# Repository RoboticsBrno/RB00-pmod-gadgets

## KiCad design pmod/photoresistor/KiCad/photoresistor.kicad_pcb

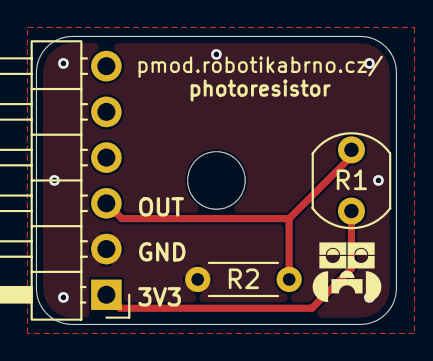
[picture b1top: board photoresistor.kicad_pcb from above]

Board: 2 copper layers, 20.0 x 16.0 mm, 4 parts (0 on the bottom side), 3 nets.

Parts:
H1: MountingHole_Pad; MountingHole_3.2mm_M3_DIN965
J2: Conn_01x06_Pin; PinHeader_1x06_P2.54mm_Horizontal
R1: LDR07; R_LDR_5.1x4.3mm_P3.4mm_Vertical
R2: R; R_Axial_DIN0204_L3.6mm_D1.6mm_P5.08mm_Horizontal

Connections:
+3V3: J2.1, R1.1
GND: J2.2, R2.2
GPIO: J2.3, R1.2, R2.1

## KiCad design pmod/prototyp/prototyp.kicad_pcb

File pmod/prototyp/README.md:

# Prototypovací modul PMOD

Tento modul slouží jako flexibilní platforma pro experimentování a rychlé vytváření prototypů elektronických obvodů. Nabízí základní PMOD konektor pro snadné připojení a testování různých komponent.

[Manuál](manual.md){ .md-button .md-button--primary }

|  |  |
| --- | --- |

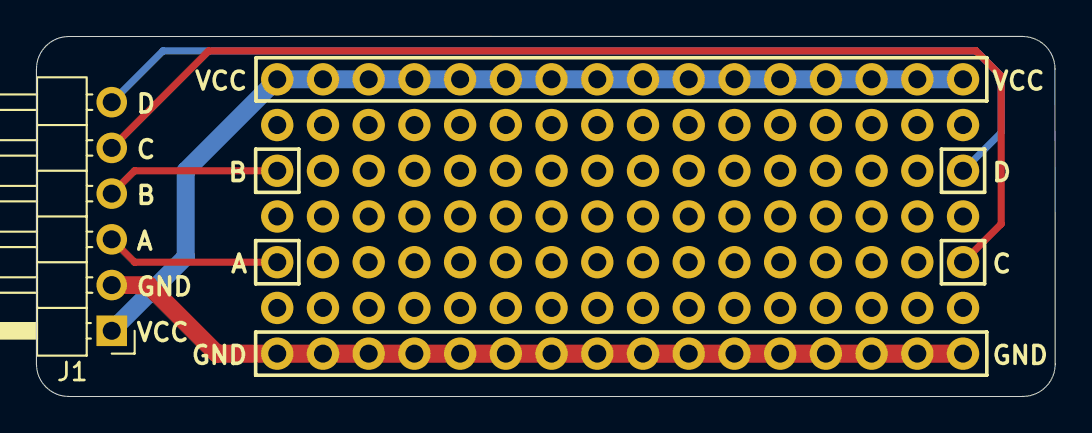
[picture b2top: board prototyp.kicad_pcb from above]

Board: 2 copper layers, 56.6 x 20.0 mm, 113 parts (0 on the bottom side), 6 nets.

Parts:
H1, H2, H3, H4, H5, H6, H7, H8, H9, H10, H11, H12, H13, H14, H15, H16, H17, H18, H19, H20, H21, H22, H23, H24, H25, H26, H27, H28, H29, H30, H31, H32, H33, H34, H35, H36, H37, H38, H39, H40, H41, H42, H43, H44, H45, H46, H47, H48, H49, H50, H51, H52, H53, H54, H55, H56, H57, H58, H59, H60, H61, H62, H63, H64, H65, H66, H67, H68, H69, H70, H71, H72, H73, H74, H75, H76, H77, H78, H79, H80, H81, H82, H83, H84, H85, H86, H87, H88, H89, H90, H91, H92, H93, H94, H95, H96, H97, H98, H99, H100, H101, H102, H103, H104, H105, H106, H107, H108, H109, H110, H111, H112: Hole
J1: Conn_01x06_Pin; PinHeader_1x06_P2.54mm_Horizontal

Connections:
A: H33.1, J1.3
B: H65.1, J1.4
C: H48.1, J1.5
D: H80.1, J1.6
GND: H1.1, H2.1, H3.1, H4.1, H5.1, H6.1, H7.1, H8.1, H9.1, H10.1, H11.1, H12.1, H13.1, H14.1, H15.1, H16.1, J1.2
VCC: H97.1, H98.1, H99.1, H100.1, H101.1, H102.1, H103.1, H104.1, H105.1, H106.1, H107.1, H108.1, H109.1, H110.1, H111.1, H112.1, J1.1

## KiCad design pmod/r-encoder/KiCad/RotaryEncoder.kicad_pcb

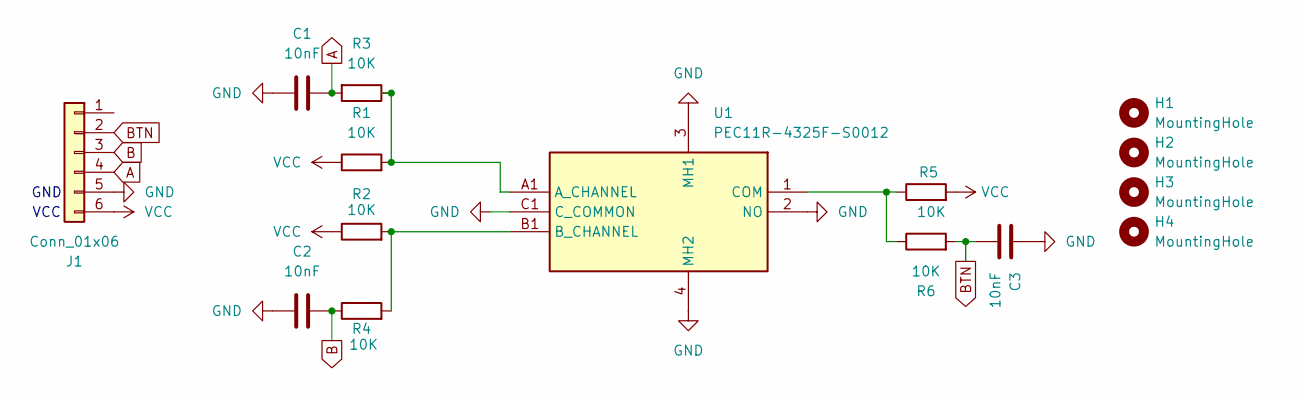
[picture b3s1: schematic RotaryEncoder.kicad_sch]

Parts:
C1, C2, C3: 10nF; C_Disc_D3.8mm_W2.6mm_P2.50mm
H1, H2, H3, H4: MountingHole; MountingHole_3.2mm_M3
J1: Conn_01x06; PinHeader_1x06_P2.54mm_Horizontal
R1, R2, R3, R4, R5, R6: 10K; R_Axial_DIN0204_L3.6mm_D1.6mm_P5.08mm_Horizontal
U1: PEC11R-4325F-S0012; PEC11R4325FS0012; Mouser Part Number 652-PEC11R4325FS0012

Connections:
A: C1.2, J1.4, R3.2
B: C2.2, J1.3, R4.1
BTN: C3.1, J1.2, R6.2
GND: C1.1, C2.1, C3.2, J1.5, U1.2 (NO), U1.3 (MH1), U1.4 (MH2), U1.C1 (C_COMMON)
unnamed: R1.2, R3.1, U1.A1 (A_CHANNEL)
unnamed: R2.2, R4.2, U1.B1 (B_CHANNEL)
unnamed: R5.1, R6.1, U1.1 (COM)
VCC: J1.6, R1.1, R2.1, R5.2

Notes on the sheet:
VCC
GND

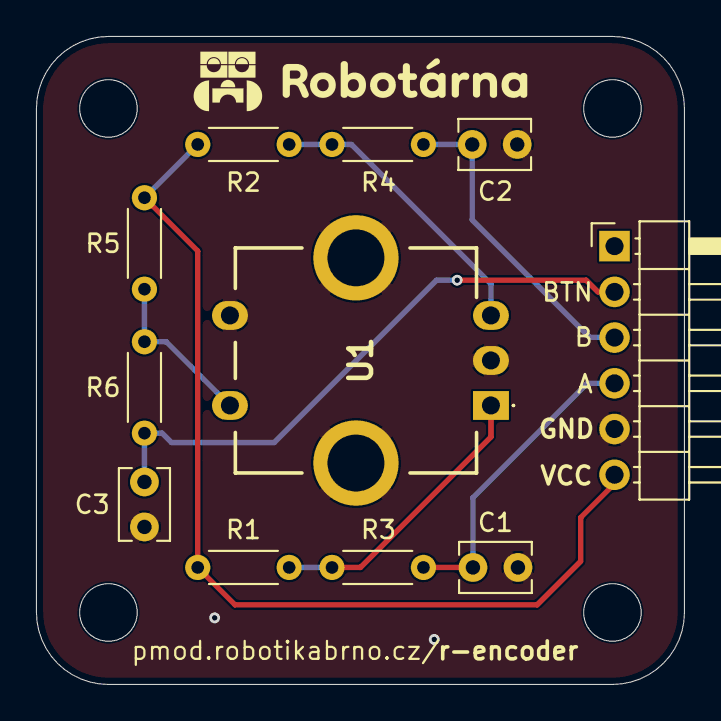
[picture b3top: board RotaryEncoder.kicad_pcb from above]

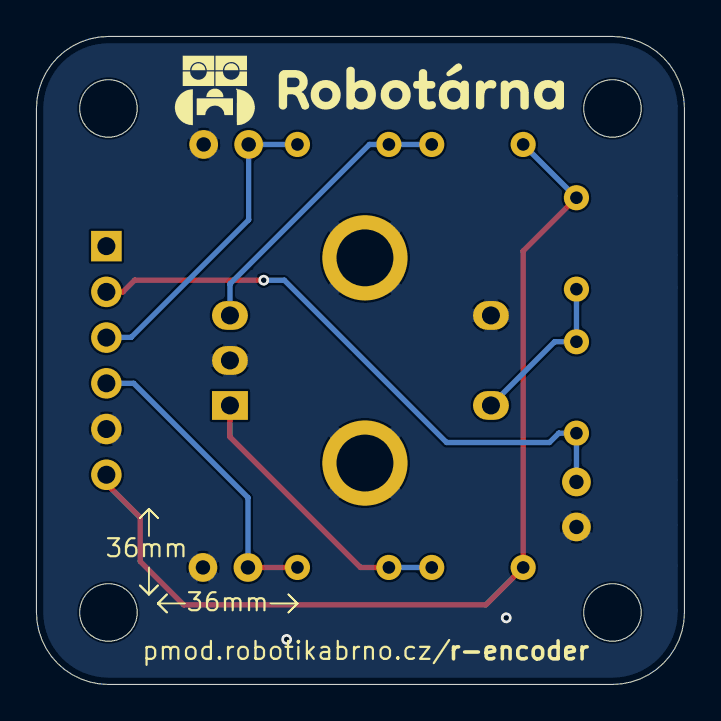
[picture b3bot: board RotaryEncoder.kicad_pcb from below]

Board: 2 copper layers, 36.0 x 36.0 mm, 15 parts (4 on the bottom side), 8 nets.

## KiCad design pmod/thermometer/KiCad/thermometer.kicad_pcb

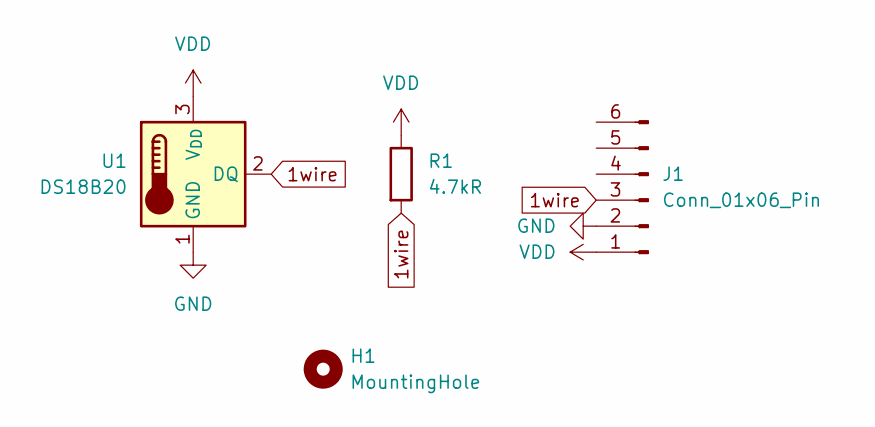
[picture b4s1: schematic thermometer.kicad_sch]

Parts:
H1: MountingHole; MountingHole_3.2mm_M3
J1: Conn_01x06_Pin; PinHeader_1x06_P2.54mm_Horizontal
R1: 4.7kR; R_Axial_DIN0207_L6.3mm_D2.5mm_P7.62mm_Horizontal
U1: DS18B20; TO-92_Inline_W4.0mm_Horizontal_FlatSideDown

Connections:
1wire: J1.3, R1.2, U1.2 (DQ)
GND: J1.2, U1.1 (GND)
VDD: J1.1, R1.1, U1.3 (V_{DD})

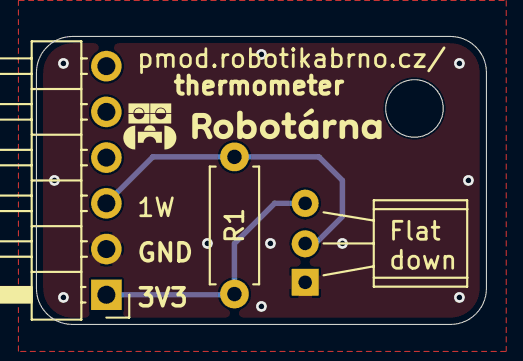
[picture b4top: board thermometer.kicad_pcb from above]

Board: 2 copper layers, 25.0 x 16.0 mm, 4 parts (0 on the bottom side), 3 nets.
